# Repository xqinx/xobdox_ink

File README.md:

# xobdox:ink
xobdox:ink is designed to work with [xobdox](https://github.com/xqinx/xobdox) as
an addon display. However due to its small footprint it is also suitable for a
wearable device, and as a matter of fact I write the firmware (still WIP) for it
to be a smart watch first, the keyboard display firmware will follow soon.

## Features
* SeeedStudio Xiao BLE module based
* 1.02 inch e-ink display

### Smart Watch
#### Battery Life
|Battery capacity | Days(BLE off) | Days(BLE on) |
|-----------------|---------------|--------------|
|160mAh           |   5  |   3   |
|250mAh           |   7  |   5   |

*Note* I have not optimize the battery life yet, there're quite a few things I
can do to make it last longer

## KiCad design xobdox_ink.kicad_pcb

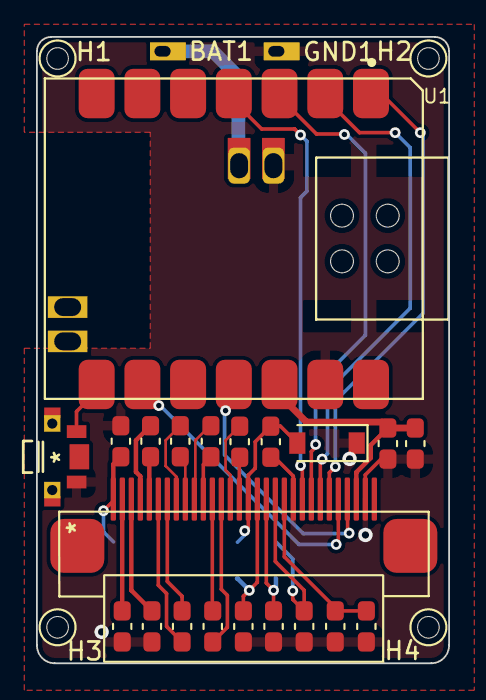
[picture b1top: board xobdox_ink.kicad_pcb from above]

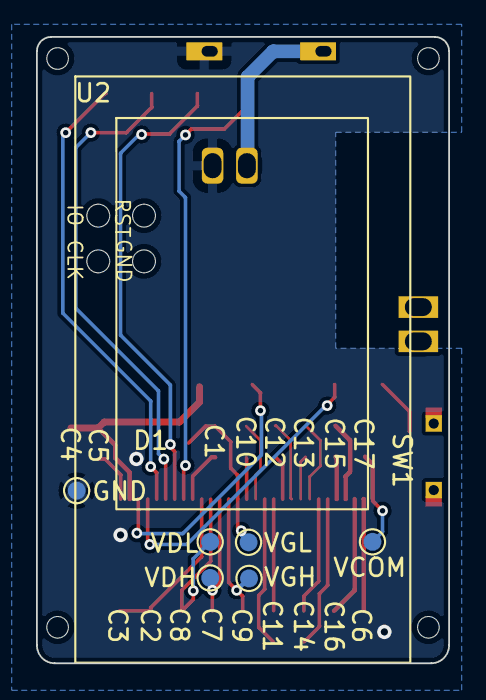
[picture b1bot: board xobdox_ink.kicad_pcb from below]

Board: 2 copper layers, 22.9 x 34.8 mm, 34 parts (7 on the bottom side), 30 nets.

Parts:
BAT1: Conn_01x01; PAD_AWG26
C1, C3, C7, C8, C9, C10, C11, C12, C13, C14, C16, C17: 1uF/50V; C_0603_1608Metric_Pad1.08x0.95mm_HandSolder
C2, C5: 0.1uF/25V; C_0603_1608Metric_Pad1.08x0.95mm_HandSolder
C4: 4.7uF/25V; C_0603_1608Metric_Pad1.08x0.95mm_HandSolder
C6, C15: 2.2uF/25V; C_0603_1608Metric_Pad1.08x0.95mm_HandSolder
D1: MBR0530; D_SOD-123
GND: TestPoint; TestPoint_Pad_D1.0mm
GND1: Conn_01x01; PAD_AWG26
H1, H2, H3, H4: MountingHole; HOLE_M1
LIPO1: BAT_LIPO; lipo_401525
SW1: SW_Push; SW_EVP-AKE31A_PAN
U1: XIAO-BLE; XIAO-BLE-SWD-HOLE
U2: EPD30; EPD_1.02_Outline
VCOM: TestPoint; TestPoint_Pad_D1.0mm
VDH: TestPoint; TestPoint_Pad_D1.0mm
VDL: TestPoint; TestPoint_Pad_D1.0mm
VGH: TestPoint; TestPoint_Pad_D1.0mm
VGL: TestPoint; TestPoint_Pad_D1.0mm

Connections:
/3V3: C4.2, C5.2, U1.12 (3V3), U2.3 (VDD)
/BAT: BAT1.1, U1.BAT (VBAT+), U1.BAT_H (VBAT+)
/BUSY: U1.4 (P0.29_A3_D3), U2.9 (BUSY)
/CS: U1.1 (P0.02_A0_D0), U2.6 (CSB)
/D/C: U1.2 (P0.03_A1_D1), U2.7 (DC)
/RES: U1.3 (P0.28_A2_D2), U2.8 (RST)
/SCLK: U1.9 (P1.13_D8_SCK), U2.5 (SCL)
/SDI: U1.11 (P1.15_D10_MOSI), U2.4 (SDA)
/VCOM: C17.2, U2.30 (VCOM), VCOM.1
/VDH: C7.2, U2.13 (VDH), VDH.1
/VDL: C8.2, U2.12 (VDL), VDL.1
/VGH: C9.2, U2.14 (VGH), VGH.1
/VGL: C1.2, D1.2 (A), U2.15 (VGL), VGL.1
GND: C1.1, C2.1, C3.1, C4.1, C5.1, C6.1, C7.1, C8.1, C9.1, C16.1, C17.1, D1.1 (K), GND.1, GND1.1, SW1.1, U1.13 (GND), U1.GND (VBAT-), U1.GND_H (VBAT-), U2.2 (GND), U2.10 (BS)
unnamed: C2.2, C3.2, U2.11 (VDDD)
unnamed: C6.2, U2.29 (VCOMH)
unnamed: C10.1, U2.17 (C6P)
unnamed: C10.2, U2.16 (C6N)
unnamed: C11.1, U2.19 (C5P)
unnamed: C11.2, U2.18 (C5N)
unnamed: C12.1, U2.21 (C4P)
unnamed: C12.2, U2.20 (C4N)
unnamed: C13.1, U2.23 (C3P)
unnamed: C13.2, U2.22 (C3N)
unnamed: C14.1, U2.25 (C2P)
unnamed: C14.2, U2.24 (C2N)
unnamed: C15.1, U2.27 (C1P)
unnamed: C15.2, U2.26 (C1N)
unnamed: C16.2, U2.28 (VCOML)
unnamed: SW1.2, U1.8 (P1.12_D7_RX)

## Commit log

2024-03-30 init commit
2024-03-30 add schematic and gerber
2024-03-30 add README and LICENSE
